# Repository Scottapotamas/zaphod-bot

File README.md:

# ZaphodBot Lightpainting Robot

ZaphodBot is a DIY, 'high-end' rotary delta robot designed primarily for high-fidelity light painting.

It's served as a personal project where the majority of mechanics, electronics, firmware and higher level software has been designed from scratch (because why not).

I've detailed the design motivation and build in a more [longform post here](https://electricui.com/blog/delta-bot).

## Mechanics

CAD files for the robot are in Solidworks 2015 format, and can be found in `/mechanical/design/`.

The power supply and main electronics stacks live inside the hexagonal structure which forms the base, with servos mounted on top, connected directly to the arms.

To manufacture parts, see `/mechanical/design/manf_outputs/`  for drawings, STEP/DXF files. SLA 3D printing was used for joints, and CNC machining for the aluminium parts and carbon plates. 

All fasteners are standard metric hex bolts, with the exception of some bottom mounting holes which are 1/4in and 3/8in threaded holes to suit typical camera tripods.

## Electronics

The PCB was designed using KiCAD 5, located in `electronics/zaphod-controller`. Gerber outputs are available with BoM, but minor design revisions are needed to improve wire-loom layout and debug/expansion connector positions. 

It's based on a STM32F4 processor, provides regulated 3/5/12V from the 75V system supply, and manages the servos, internal IO and external IO.

- Power input (75V from Teknic IPC) through 2-pin MOLEX SABRE connector.
- Clearpath servo motors connect with 8-pin MOLEX MicroFit for signalling, and 4-pin MicroFit for 75V supply.
- Internal IO NanoFit connectors provide PWM fan support, UART, I2C, 2x ADC/DAC, and PWM. These can also be used as generic IO. See  `/electronics/zaphod-controller/Outputs/zaphod-controller-sch.pdf` for pinouts.
- Internal IO 2.54mm header strip provides switchable+fused 3.3V and USART, intended for wireless comms backpack in the future (likely ESP32 flavoured).
- The 9-pin LEMO connector used for external expansion provides galvanically isolated USB and 4 isolated IO lines (2 inputs, 2 outputs). Pinout in `/docs/connectors_pinouts.md`.
- The 7-pin LEMO connector supports a 4th Clearpath SD series servo, intended for use with rotating or linear stages. Pinout in `/docs/connectors_pinouts.md.`

## Firmware

Microcontroller firmware (STM32) is in `/firmware`, is written in C, and can be built with a fairly standard `arm-gcc-eabi-none` toolchain.

I've used (and included config for) CLion as my main IDE, which is CMake based, though building with SW4/Eclipse shouldn't be too hard either.

Flashing the microcontroller is pretty standard as well, a 10-pin ARM CORTEX SWD socket is on the PCB, which connects to a STLink, Blackmagic Probe, or JLink programmer (used all three at various stages of this project).

# User Interface

The user interface is built with [Electric UI](https://electricui.com/install), and can be built and run by invoking `arc start` from `/interface`. 

It facilitates control and monitoring of the hardware, along with toolpath generation, optimisation and visualisation pipelines.

## Toolpath Generation

Toolpaths for lightpainting are created by exporting spline data from [Blender using a Python script](https://github.com/Mike-Dax/total-perspective-vortex/blob/main/blender/addons/total_perspective_vortex/tpv.py), and loading the output with the "Blender" tab in the UI.

The frontend UI is responsible for parsing the Blender scene and performing a series of move planning and TSP optimisation steps to reduce render times.

https://user-images.githubusercontent.com/460325/182141536-1118c95f-b80b-4199-9833-aa961b41ea9a.mp4

> This screencap shows a Blender animation being loaded: the 'fast' plan completes within a second, then the multi-threaded TSP solver iterates on each frame to refine the path taken to render the particles.

# Accessories

## Light Painting

The light-painting 'brush' uses acrylic 1mm core fibre, connected to a 3x3W RGB LED.

The fibre is mounted to the effector with a turned acetal stalk (not documented), or with one of the SLA printed mounts found in `/mechanical/fibre-couplers/`.

The driver PCB is in `/electronics/rgb-led-board/` along with manufacturing files and a simple Arduino test program. This board connects to `zaphod-controller` via the 8-pin NanoFit connector, which provides PWM+IO and power.

## External E-STOP + IO Breakout Box

The 9-pin LEMO connector is used with a 2m cable, connecting to the breakout box via matching 9-pin LEMO. A [Novelkeys Big Switch](https://novelkeys.xyz/products/the-big-switch-series) is used as an E-STOP, with the keyswitch light indicating motor state.

A 2.5mm stereo socket mounted in the box provides support for camera shutter release cable, in this case for a Canon N3 connector.

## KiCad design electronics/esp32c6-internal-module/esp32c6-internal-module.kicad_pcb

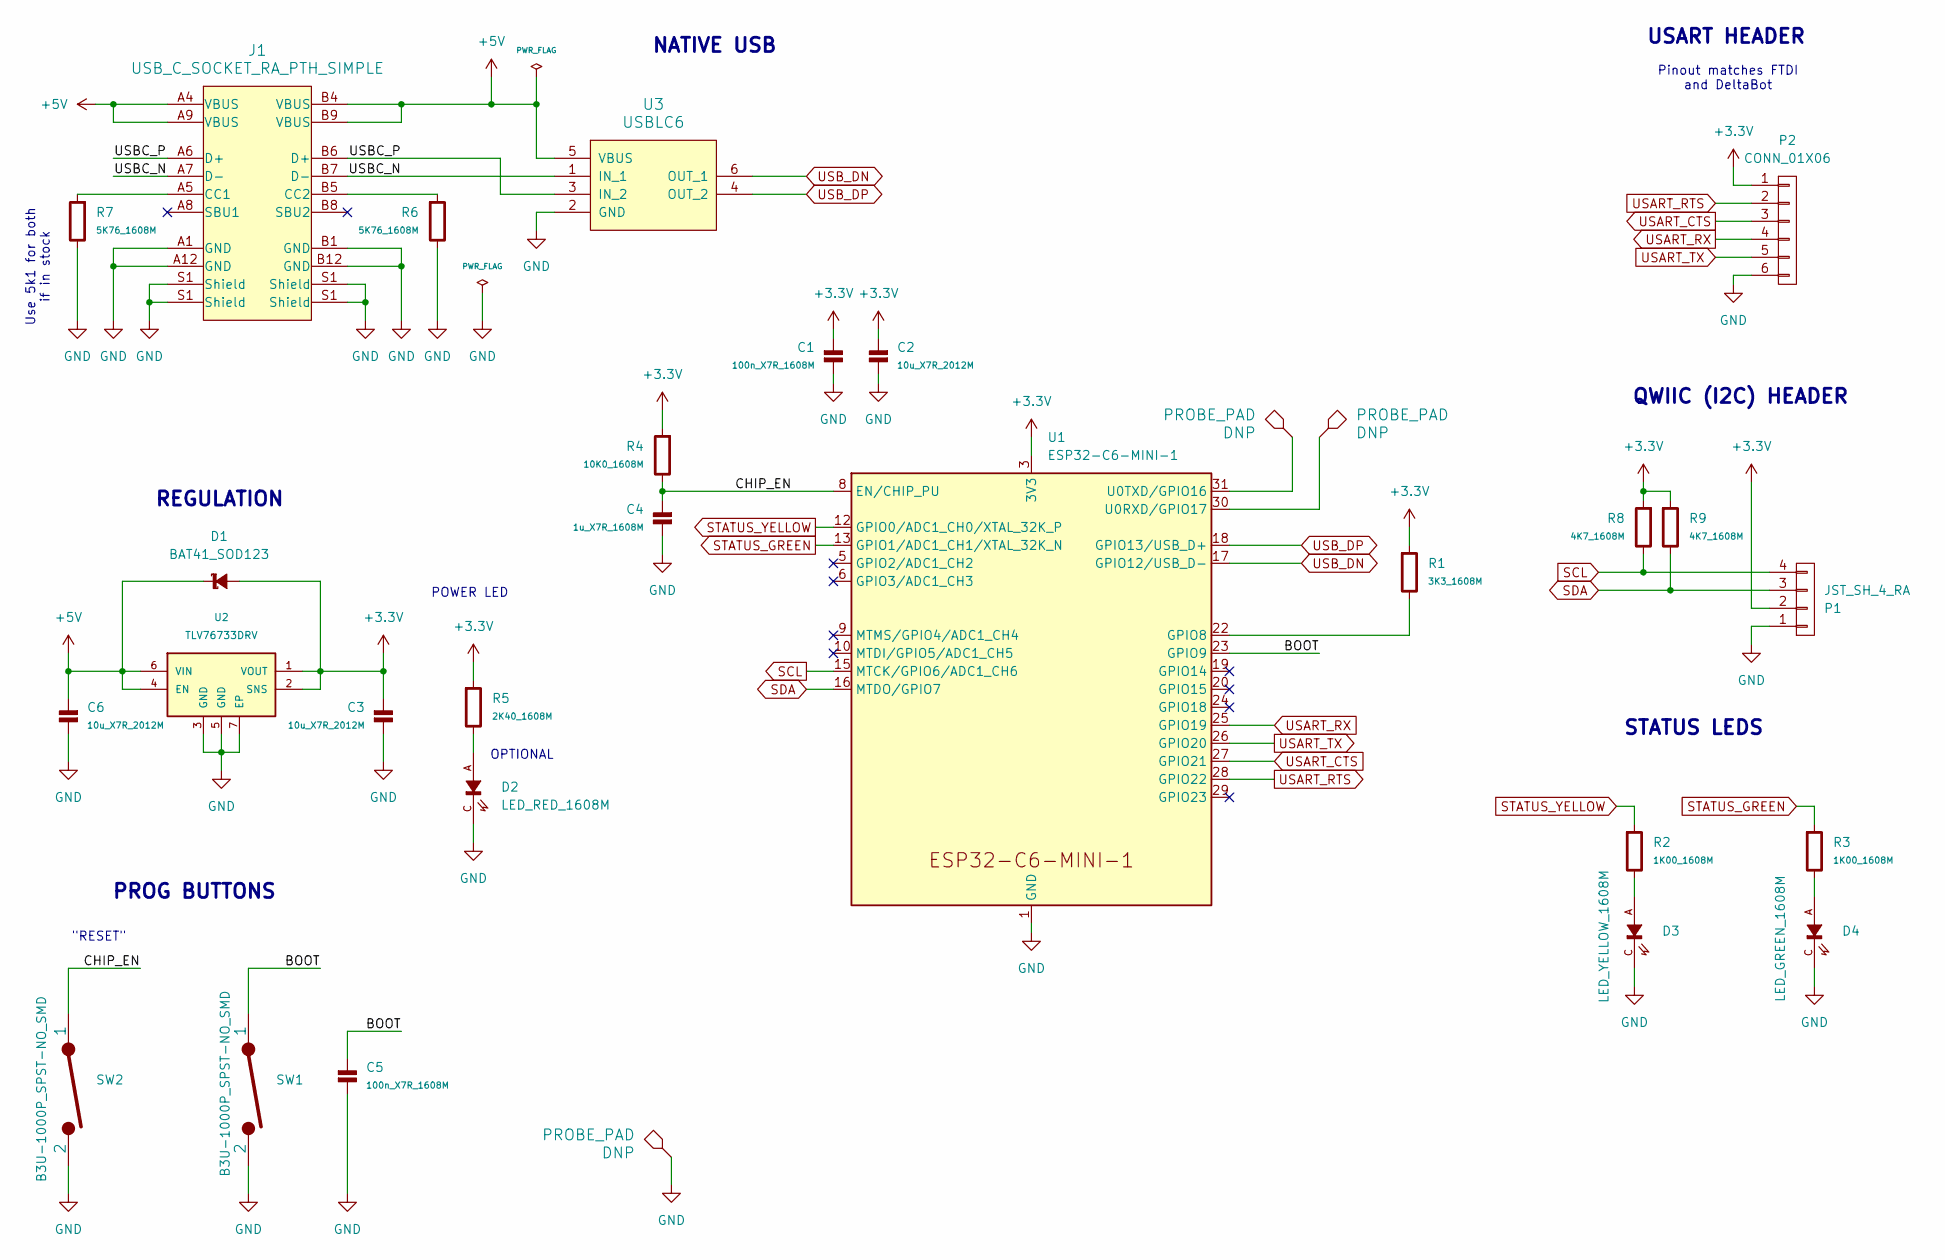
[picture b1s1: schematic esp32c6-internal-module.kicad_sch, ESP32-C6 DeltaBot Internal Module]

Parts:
C1, C5: 100n_X7R_1608M; CAPC1608X90N
C2, C3, C6: 10u_X7R_2012M; CAPC2012X110N
C4: 1u_X7R_1608M; CAPC1608X90N
D1: BAT41_SOD123; SOD3715X145L
D2: LED_RED_1608M; LEDC1608X80L40N
D3: LED_YELLOW_1608M; LEDC1608X80L40N
D4: LED_GREEN_1608M; LEDC1608X80L40N
J1: USB_C_SOCKET_RA_PTH_SIMPLE; USB_C_PTH_GCT_USB4085
P1: JST_SH_4_RA; SM04B-SRSS-TB
P2: CONN_01X06; 61300611121
R1: 3K3_1608M; RESC1608X50N
R2, R3: 1K00_1608M; RESC1608X50N
R4: 10K0_1608M; RESC1608X50N
R5: 2K40_1608M; RESC1608X50N
R6, R7: 5K76_1608M; RESC1608X50N
R8, R9: 4K7_1608M; RESC1608X50N
SW1, SW2: B3U-1000P_SPST-NO_SMD; B3U-1000P
TEST1, TEST2, TEST3: PROBE_PAD; TP100
U1: ESP32-C6-MINI-1
U2: TLV76733DRV; SON65P200X200X80-9T160X100N
U3: USBLC6; SOT95P280X145-6L50N

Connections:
+3.3V: C1.1, C2.1, C3.1, D1.A, P1.2, P2.1, R1.1, R4.1, R5.1, R8.1, R9.1, U1.3 (3V3), U2.1 (VOUT), U2.2 (SNS)
+5V: C6.1, D1.C, J1.A4 (VBUS), J1.A9 (VBUS), J1.B4 (VBUS), J1.B9 (VBUS), U2.4 (EN), U2.6 (VIN), U3.5 (VBUS)
/BOOT: C5.1, SW1.1, U1.23 (GPIO9)
/CHIP_EN: C4.1, R4.2, SW2.1, U1.8 (EN/CHIP_PU)
/USBC_N: J1.A7 (D-), J1.B7 (D-), U3.1 (IN_1)
/USBC_P: J1.A6 (D+), J1.B6 (D+), U3.3 (IN_2)
GND: C1.2, C2.2, C3.2, C4.2, C5.2, C6.2, D2.C, D3.C, D4.C, J1.A1 (GND), J1.A12 (GND), J1.B1 (GND), J1.B12 (GND), J1.S1 (Shield), P1.1, P2.6, R6.2, R7.2, SW1.2, SW2.2, TEST3.1 (PAD), U1.1 (GND), U1.2 (GND), U1.11 (GND), U1.14 (GND), U1.36 (GND), U1.37 (GND), U1.38 (GND), U1.39 (GND), U1.40 (GND), U1.41 (GND), U1.42 (GND), U1.43 (GND), U1.44 (GND), U1.45 (GND), U1.46 (GND), U1.47 (GND), U1.48 (GND), U1.49 (GND), U1.50 (GND), U1.51 (GND), U1.52 (GND), U1.53 (GND), U2.3 (GND), U2.5 (GND), U2.7 (EP), U3.2 (GND)
unnamed: D3.A, R2.2
unnamed: D4.A, R3.2
unnamed: D2.A, R5.2
unnamed: J1.A5 (CC1), R7.1
unnamed: J1.B5 (CC2), R6.1
unnamed: TEST1.1 (PAD), U1.31 (U0TXD/GPIO16)
unnamed: TEST2.1 (PAD), U1.30 (U0RXD/GPIO17)
unnamed: R1.2, U1.22 (GPIO8)
SCL: P1.4, R8.2, U1.15 (MTCK/GPIO6/ADC1_CH6)
SDA: P1.3, R9.2, U1.16 (MTDO/GPIO7)
STATUS_GREEN: R3.1, U1.13 (GPIO1/ADC1_CH1/XTAL_32K_N)
STATUS_YELLOW: R2.1, U1.12 (GPIO0/ADC1_CH0/XTAL_32K_P)
USART_CTS: P2.3, U1.27 (GPIO21)
USART_RTS: P2.2, U1.28 (GPIO22)
USART_RX: P2.4, U1.25 (GPIO19)
USART_TX: P2.5, U1.26 (GPIO20)
USB_DN: U1.17 (GPIO12/USB_D-), U3.6 (OUT_1)
USB_DP: U1.18 (GPIO13/USB_D+), U3.4 (OUT_2)

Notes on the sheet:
NATIVE USB
PROG BUTTONS
Pinout matches FTDI and DeltaBot
"RESET"
QWIIC (I2C) HEADER
OPTIONAL
REGULATION
USART HEADER
Use 5k1 for both if in stock
POWER LED
STATUS LEDS

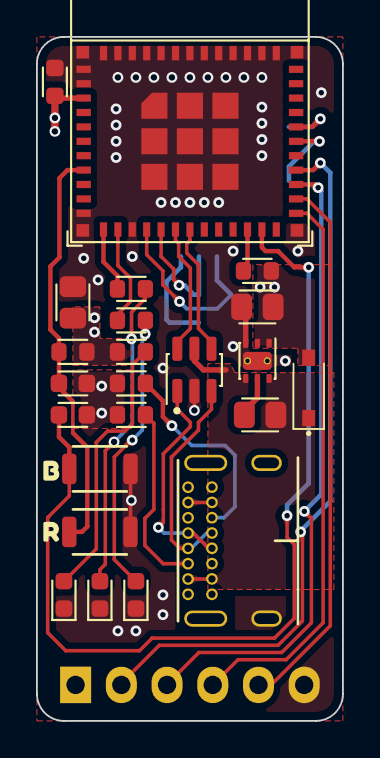
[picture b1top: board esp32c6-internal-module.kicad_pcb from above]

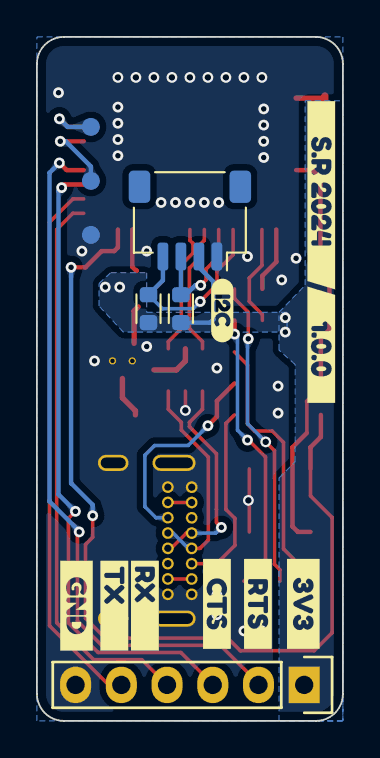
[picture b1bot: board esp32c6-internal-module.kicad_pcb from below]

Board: 2 copper layers, 17.0 x 38.0 mm, 41 parts (16 on the bottom side), 25 nets.

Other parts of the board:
kibuzzard-667148AD: G***; kibuzzard-667148AD
kibuzzard-667148E1: G***; kibuzzard-667148E1
kibuzzard-6671475C: G***; kibuzzard-6671475C
kibuzzard-6671480C: G***; kibuzzard-6671480C
kibuzzard-6671482E: G***; kibuzzard-6671482E
kibuzzard-66714795: G***; kibuzzard-66714795
kibuzzard-66714802: G***; kibuzzard-66714802
kibuzzard-66714835: G***; kibuzzard-66714835
kibuzzard-66714898: G***; kibuzzard-66714898
kibuzzard-66714909: G***; kibuzzard-66714909
kibuzzard-66714928: G***; kibuzzard-66714928

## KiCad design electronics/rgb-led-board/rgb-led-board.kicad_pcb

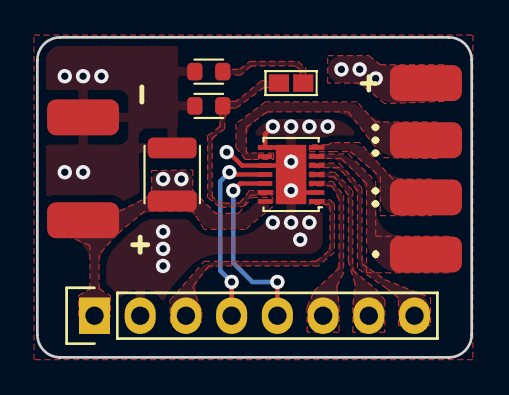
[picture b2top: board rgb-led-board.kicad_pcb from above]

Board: 2 copper layers, 24.1 x 17.8 mm, 12 parts (0 on the bottom side), 13 nets.

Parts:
C1: 22u_X7R_3225M; CAPC3225X170N
P1, P2, P4, P5, P6, P7: PAD_SOLDER_2mm
P3: CONN_01X08; 61300811121
R1, R2: 12K7_1608M; RESC1608X50N
SL1: SOLDER-LINK-2; SJ1608-2N
U1: AL1793AFE-13; QFN14P50_400X300X65L40X25N

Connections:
+POWER: C1.1, P1.1, P3.1, P4.1, U1.14
/ENABLE: P3.3, U1.1
/LED_1: P5.1, U1.6
/LED_2: P6.1, U1.7
/LED_3: P7.1, U1.9
/POWER_GOOD: P3.4, U1.11
/PWM1: P3.8, U1.5
/PWM2: P3.7, U1.4
/PWM3: P3.6, U1.3
/~FAULT: P3.5, U1.12
GND: C1.2, P2.1, P3.2, R1.2, R2.2, U1.2, U1.8, U1.10, U1.15
unnamed: R1.1, SL1.1
unnamed: R2.1, SL1.2, U1.13

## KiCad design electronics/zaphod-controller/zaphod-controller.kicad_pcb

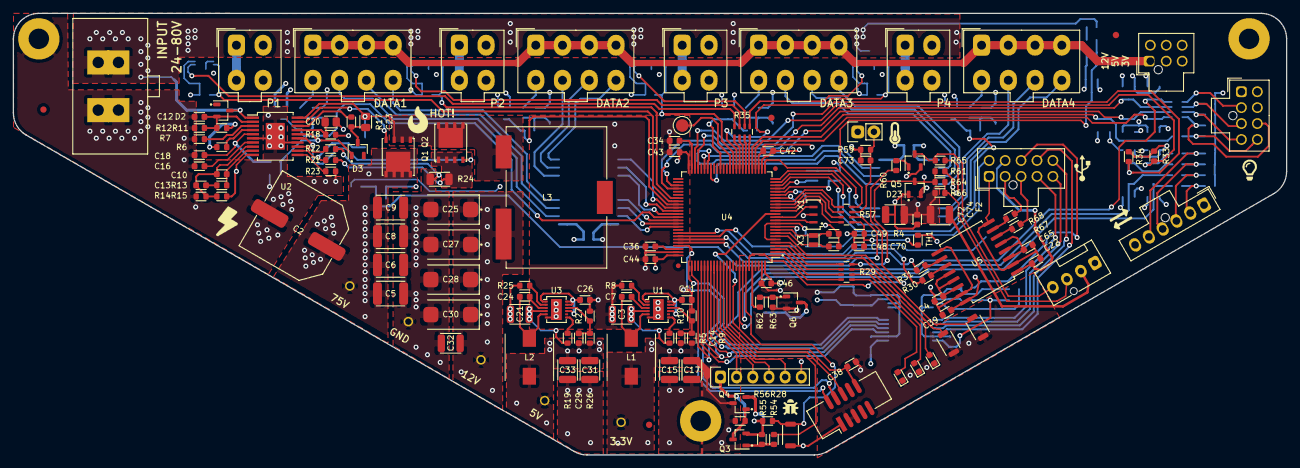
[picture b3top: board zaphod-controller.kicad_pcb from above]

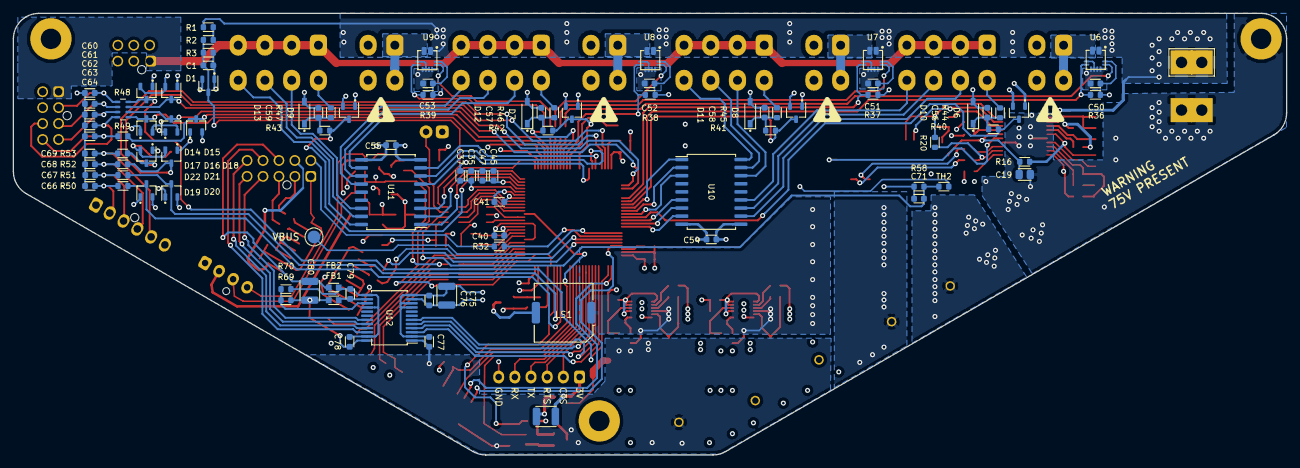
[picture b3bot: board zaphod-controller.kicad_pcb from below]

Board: 4 copper layers, 199.9 x 69.3 mm, 251 parts (97 on the bottom side), 182 nets.

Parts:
C1, C4, C7, C16, C22, C24, C37, C38, C39, C40, C41, C42, C43, C44, C46, C47, C50, C51, C52, C53, C54, C55, C65, C70, C71, C73, C74, C76, C77, C78, C79: 100n_X7R_1608M; CAPC1608X90N
C2: 47u_ELEC_100V_1350X1350M; CAPAE1350X1350D1490DD450L470N
C3, C21, C75, C80: 10u_X7R_3225M; CAPC3225X170N
C5, C6, C8, C9: 2u2_X7R_4532M; CAPC4532X180N
C10: 15p_X7R_1608M; CAPC1608X90N
C11, C12, C26, C34, C35, C36, C45: 1u_X7R_1608M; CAPC1608X90N
C13: 1n5_X7R_1608M; CAPC1608X90N
C14, C29, C48, C49: 22p_X7R_1608M; CAPC1608X90N
C15, C17, C31, C32, C33, C72: 22u_X7R_3225M; CAPC3225X170N
C18: 330p_X7R_1608M; CAPC1608X90N
C19, C20, C23: 1u_X7R_2012M; CAPC2012X110N
C25, C27, C28, C30: 47u_TANT_7343M; CAPPM7343X310N
C56, C57, C58, C59: 10n_X7R_1608M; CAPC1608X90N
C60, C61, C62, C63, C64, C66, C67, C68, C69: 1n_X7R_1608M; CAPC1608X90N
D1, D6, D7, D8, D9, D14, D15, D16, D17, D18, D19, D20, D21, D22, D23: BAV99; SOT95P240X110-3L16N
D2, D3: 200V_350mW_SOT23; SOT95P240X110-3L16N
D4: LED_YELLOW_1608M; LEDC1608X80L40N
D5: LED_GREEN_1608M; LEDC1608X80L40N
D10, D11, D12, D13: 3V3; SOD3715X145N
D24: LED_RED_1608M; LEDC1608X80L40N
F1, F2: 0.5A_1210L_PTC; FUSC3225X85L50N
FB1, FB2: 1K_1608M; INDC1608X95N
FID1, FID2, FID3, FID4: FIDUCIAL; FID100X200
L1, L2: 22u_MCSDRH73B; INDM7373X355L170X207N
L3: 10u2_PA2050; PULSE_PA2050
LOGO1: LOGO; PANIC_LOGO890X810
LOGO2: LOGO; BUG_LOGO250X250
LOGO3: LOGO; BULB_LOGO230X330
LOGO4: LOGO; THERMO_LOGO_170X350
LOGO5: LOGO; USB_LOGO410X250
LOGO6, LOGO7, LOGO8, LOGO9: LOGO; WARN_TRIANGLE_LOGO440X400
LOGO10: LOGO; WARN_TRIANGLE_LOGO440X400_MASK
LOGO11: LOGO; FIRE_LOGO_320X420
LOGO12: LOGO; BOLT_LOGO_310X490
LOGO13: LOGO; DUPLEX_LOGO330X260
LS1: PKMCS0909E4000-R1; MURATA_PKMCS0909E4000
MNT1, MNT2, MNT3: MNT_M3_PLATED; MTGP650H330
P1: MOLEX_43160-0102; Molex_Sabre_43160-0102_VERT
P2, P3, P4, P5: MOLEX_MINIFIT_JR_2x2_WAY; Molex_Mini-Fit_Jr_5566-04A_2x02_P4.20mm_Vertical
P11, P12, P13, P14: MOLEX_MINIFIT_JR_2x4_WAY; Molex_Mini-Fit_Jr_5566-08A_2x04_P4.20mm_Vertical
P15: MOLEX_NANOFIT_2x4_WAY; Molex_Nano-Fit_105310-xx08_2x04_VERT
P16: MOLEX_NANOFIT_1x6_WAY; Molex_Nano-Fit_105309-xx06_1x06_VERT
P17: MOLEX_NANOFIT_2x3_WAY; Molex_Nano-Fit_105310-xx06_2x03_VERT
P18: CONN_01X02; 61300211121
P19: MOLEX_KK2.54_1x4_WAY_FAN; MOLEX_47053-1000
P20: CONN_01X06; 61300611121
P21: MOLEX_NANOFIT_2x5_WAY; Molex_Nano-Fit_105310-xx10_2x05_VERT
Q1, Q2: Si7852DP; SON127P490X575X90-9T313X381N
Q3, Q6: 2N7002P; SOT95P240X110-3L16N
Q4: NTR1P02T1G; SOT95P240X110-3L16N
Q5: BC847B; SOT95P240X110-3L16N
R1, R2: 130K_1608M; RESC1608X50N
R3, R23, R36, R37, R38, R39, R55, R56, R61, R63, R70: 10K0_1608M; RESC1608X50N
R4, R58, R59: 2K40_1608M; RESC1608X50N
R5, R8, R9, R19, R25, R28: 100K_1608M; RESC1608X50N
R6: 1M_1608M; RESC1608X50N
R7, R27: 12K7_1608M; RESC1608X50N
R10, R44, R45, R46, R47: 22K_1608M; RESC1608X50N
R11: 102K_1608M; RESC1608X50N
R12: 9K53_1608M; RESC1608X50N
R13: 39K_1608M; RESC1608X50N
R14: 1K2_1608M; RESC1608X50N
R15: 10K7_1608M; RESC1608X50N
R16: 750K_1608M; RESC1608X50N
R17: 2R2_1608M; RESC1608X50N
R18: 1R0_1608M; RESC1608X50N
R20, R21, R22: 0R_1608M; RESC1608X50N
R24: R01_3216M; RESC3216X140N
R26: 91K_1608M; RESC1608X50N
R29, R35, R57: 1K_QUAD_ARRAY_1608M; R_Array_Concave_4x1608M
R30, R31, R67, R68: 22R_1608M; RESC1608X50N
R32, R40, R41, R42, R43, R50, R51: 100R_1608M; RESC1608X50N
R33, R34, R65, R66: 4K7_1608M; RESC1608X50N
R48: 47R_QUAD_ARRAY_1608M; R_Array_Concave_4x1608M
R49, R52, R53, R54, R62: 10R_1608M; RESC1608X50N
R60: 1K00_1608M; RESC1608X50N
R64: 33K2_1608M; RESC1608X50N
R69: 16K9_1608M; RESC1608X50N
SW1, SW2, SW3: B3U-1000P_SPST-NO_SMD; B3U-1000P
TEST1: CLIP_HOOK_BROWN; KEYSTONE_5115
TEST2: CLIP_HOOK_YELLOW; KEYSTONE_5004
TEST3: CLIP_HOOK_RED; KEYSTONE_5000
TEST4: CLIP_HOOK_ORANGE; KEYSTONE_5003
TEST5: CLIP_HOOK_BLACK; KEYSTONE_5001
TEST6, TEST8: PROBE_PAD; TP200
TH1, TH2: NTC_10K_1608M; RESC1608X50N
U1, U3: ISL85410FRZ; QFN50P400X300X100-13T170X330N
U2: LM5116; SOP21P65_720X780X200L75X30N
U4: STM32F429VET6; QFP50P1600X1600X160-100L25N
U5: ADUM3160; SOIC127P1032X265-16L87N
U6, U7, U8, U9: ACS711KEXLT_15AB; ACS-EX-12
U10, U11: ULN2003A; SOIC127P1030X265-18L87N
U12: ADUM5412; SOP65P780X200-24L40N
X1: CSTCE8M00G55Z; OSCSC-CSCTE-CERALOCK
X2: SWD_SMT_SOCKET; CNCTECH_3220-10-0300-00
X3: ABS06-107-32.768KHZ; XTALDFN200X120X60-2N

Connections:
+3.3V: C14.1, C15.1, C17.1, C35.1, C37.1, C39.2, C40.1, C41.1, C42.1, C43.1, C44.1, C45.1, C46.1, C47.1, C50.2, C51.2, C52.2, C53.2, C77.2, D1.2, D6.2, D7.2, D8.2, D9.2, D14.2, D15.2, D16.2, D17.2, D18.2, D19.2, D20.2, D21.2, D22.2, D23.2, L1.1, P15.6, P16.1, P17.3, P18.1, Q4.3, R9.1, R33.2, R34.1, R36.2, R37.2, R38.2, R39.2, R56.1, SW1.2, TEST4.1, TH1.1, TH2.1, U4.6, U4.11, U4.19, U4.21, U4.22, U4.28, U4.50, U4.75, U4.100, U5.16, U6.12, U7.12, U8.12, U9.12, U12.1, X2.1
+5V: C29.1, C31.1, C33.1, C75.2, C76.2, L2.1, P17.2, R26.1, R65.2, TEST3.1, U12.11
+12V: C3.2, C21.2, C25.1, C27.1, C28.1, C30.1, C32.1, C54.2, C55.2, C72.2, C74.2, F2.2, L3.2, LS1.1, P11.1, P11.2, P11.3, P11.4, P12.1, P12.2, P12.3, P12.4, P13.1, P13.2, P13.3, P13.4, P14.1, P14.2, P14.3, P14.4, P15.1, P17.1, R5.2, R15.1, R18.1, R19.2, R66.2, TEST2.1, U1.4, U2.10, U3.4, U10.10, U11.10
+POWER: C2.1, C5.1, C6.1, C8.1, C9.1, D2.3, P1.1, Q1.3, R1.2, R6.2, R11.1, TEST1.1, U2.1, U6.1, U7.1, U8.1, U9.1
/Expansion I/O/ISO_IN_0: P21.5, U12.20
/Expansion I/O/ISO_IN_1: P21.4, U12.19
/Expansion I/O/ISO_IO_GND: C80.1, FB2.1, P21.8
/Expansion I/O/ISO_OUT_0: P21.9, U12.22
/Expansion I/O/ISO_OUT_1: P21.10, U12.21
/Output Circuits and Connectors/M1_PWR: P2.1, P2.3, U6.4
/Output Circuits and Connectors/M2_PWR: P3.1, P3.3, U7.4
/Output Circuits and Connectors/M3_PWR: P4.1, P4.3, U8.4
/Output Circuits and Connectors/M4_PWR: P5.1, P5.3, U9.4
AUX_ANALOG_0: D17.3, R48.5, U4.29
AUX_ANALOG_1: D18.3, R49.2, U4.30
AUX_PWM_0: D14.3, R48.8, U4.77
AUX_PWM_1: D15.3, R48.7, U4.53
AUX_PWM_2: D16.3, R48.6, U4.54
BOOT0: R28.1, SW1.1, U4.94
BOOT1: TEST8.1, U4.37
BUTTON_0: SW2.2, U4.7
BUTTON_1: SW3.2, U4.5
BUZZER_PWM: R62.2, U4.96
EXT_INPUT_0: U4.83, U12.5
EXT_INPUT_1: U4.81, U12.6
EXT_OUTPUT_0: U4.80, U12.3
EXT_OUTPUT_1: U4.82, U12.4
FAN_HALL: R29.1, U4.4
FAN_PWM: R60.2, U4.95
GND: C1.2, C2.2, C3.1, C4.1, C5.2, C6.2, C8.2, C9.2, C11.1, C12.1, C15.2, C16.2, C17.2, C18.2, C19.1, C20.1, C21.1, C25.2, C26.1, C27.2, C28.2, C30.2, C31.2, C32.2, C33.2, C34.2, C35.2, C36.2, C37.2, C38.2, C39.1, C40.2, C41.2, C42.2, C43.2, C44.2, C45.2, C46.2, C47.2, C48.2, C49.2, C50.1, C51.1, C52.1, C53.1, C54.1, C55.1, C56.1, C57.1, C58.1, C59.1, C60.2, C61.2, C62.2, C63.2, C64.2, C66.2, C67.2, C68.2, C69.2, C70.1, C71.1, C72.1, C73.1, C74.1, C75.1, C76.1, C77.1, D1.1, D4.C, D5.C, D6.1, D7.1, D8.1, D9.1, D10.A, D11.A, D12.A, D13.A, D14.1, D15.1, D16.1, D17.1, D18.1, D19.1, D20.1, D21.1, D22.1, D23.1, D24.C, MNT1.1, MNT2.1, MNT3.1, P1.2, P2.2, P2.4, P3.2, P3.4, P4.2, P4.4, P5.2, P5.4, P15.5, P16.6, P17.4, P17.5, P17.6, P19.1, P20.6, Q3.2, Q5.2, Q6.2, R3.1, R4.2, R7.1, R8.2, R10.2, R12.2, R14.2, R22.1, R23.1, R24.2, R25.2, R27.2, R28.2, R55.2, R58.2, R59.2, R61.2, R63.2, SW2.1, SW3.1, TEST5.1, U1.6, U1.EP, U2.6, U2.14, U2.EP, U3.6, U3.EP, U4.10, U4.20, U4.27, U4.74, U4.99, U5.9, U5.15, U6.5, U6.7, U6.8, U6.9, U6.10, U7.5, U7.7, U7.8, U7.9, U7.10, U8.5, U8.7, U8.8, U8.9, U8.10, U9.5, U9.7, U9.8, U9.9, U9.10, U10.9, U11.9, U12.2, U12.9, U12.10, U12.12, X1.2, X2.3, X2.5
I2C_SCK: D21.3, R34.2, R52.2, U4.47
I2C_SDA: D22.3, R33.1, R53.2, U4.48
ID_SPARE: P21.6, R32.2
ISOLATED_D+: P21.2, R68.1
ISOLATED_D-: P21.3, R67.1
ISOLATED_USB_GND: C22.1, C65.1, P21.1, U5.2, U5.8
ISOLATED_USB_VDD: C22.2, P21.7, U5.1
MOTOR_1_CURRENT: R35.5, U4.34
MOTOR_2_CURRENT: R35.6, U4.33
MOTOR_3_CURRENT: R35.7, U4.32
MOTOR_4_CURRENT: R35.8, U4.31
NRST: C38.1, U4.14, X2.10
unnamed: C1.1, D1.3, R2.1, R3.2, R57.4
unnamed: C4.2, U5.12, U5.13, U5.14
unnamed: C7.1, U1.3
unnamed: C7.2, L1.2, U1.5
unnamed: C10.1, R13.1, U2.9
unnamed: C10.2, C13.1, R14.1, R15.2, U2.8
unnamed: C11.2, U1.1, U1.9, U1.11, U1.12
unnamed: C12.2, D2.2, R11.2, R12.1, U2.2
unnamed: C13.2, R13.2
unnamed: C14.2, R9.2, R10.1, U1.10
unnamed: C16.1, U2.7
unnamed: C18.1, R16.2, U2.5
unnamed: C19.2, D3.1, R16.1, U2.16
unnamed: C20.2, R18.2, U2.17
unnamed: C23.1, L3.1, Q1.2, Q2.3, R20.1, U2.20
unnamed: C23.2, D3.3, R17.2
unnamed: C24.1, U3.3
unnamed: C24.2, L2.2, U3.5
unnamed: C26.2, U3.1, U3.9, U3.11, U3.12
unnamed: C29.2, R26.2, R27.1, U3.10
unnamed: C34.1, U4.49
unnamed: C36.1, U4.73
unnamed: C48.1, U4.8, X3.1
unnamed: C49.1, U4.9, X3.2
unnamed: C56.2, D10.C, R40.1, R44.2
unnamed: C57.2, D12.C, R42.1, R46.2
unnamed: C58.2, D11.C, R41.1, R45.2
unnamed: C59.2, D13.C, R43.1, R47.2
unnamed: C60.1, P15.2, R48.1
unnamed: C61.1, P15.3, R48.2
unnamed: C62.1, P15.4, R48.3
unnamed: C63.1, P15.7, R48.4
unnamed: C64.1, P15.8, R49.1
unnamed: C65.2, U5.3, U5.4, U5.5
unnamed: C66.1, P16.2, R50.1
unnamed: C67.1, P16.3, R51.1
unnamed: C68.1, P16.4, R52.1
unnamed: C69.1, P16.5, R53.1
unnamed: C70.2, R4.1, R57.1, TH1.2
unnamed: C71.2, R57.2, R58.1, TH2.2
unnamed: C73.2, P18.2, R57.3, R59.1
unnamed: C78.1, C79.1, FB2.2, R70.1, U12.13, U12.16, U12.23
unnamed: C78.2, C80.2, FB1.1, R69.1, U12.24
unnamed: C79.2, FB1.2, U12.14
unnamed: D4.A, R29.6
unnamed: D5.A, R29.5
unnamed: D23.3, R29.8, R61.1, R64.2
unnamed: D24.A, R29.7
unnamed: F1.1, P20.1
unnamed: F1.2, Q4.2
unnamed: F2.1, P19.2
unnamed: LS1.2, Q6.3
unnamed: P11.5, R44.1
unnamed: P11.6, U10.11
unnamed: P11.7, U10.12
unnamed: P11.8, U10.13
unnamed: P12.5, R45.1
unnamed: P12.6, U10.16
unnamed: P12.7, U10.17
unnamed: P12.8, U10.18
unnamed: P13.5, R46.1
unnamed: P13.6, U11.11
unnamed: P13.7, U11.12
unnamed: P13.8, U11.13
unnamed: P14.5, R47.1
unnamed: P14.6, U11.16
unnamed: P14.7, U11.17
unnamed: P14.8, U11.18
unnamed: P19.3, R64.1, R66.1
unnamed: P19.4, Q5.3, R65.1
unnamed: Q1.1, U2.19
unnamed: Q2.1, U2.15
unnamed: Q2.2, R21.1, R24.1
unnamed: Q3.1, R54.1, R55.1
unnamed: Q3.3, Q4.1, R56.2
unnamed: Q5.1, R60.1
unnamed: Q6.1, R62.1, R63.1
unnamed: R1.1, R2.2
unnamed: R5.1, U1.7
unnamed: R6.1, U2.4
unnamed: R7.2, U2.3
unnamed: R8.1, U1.2
unnamed: R17.1, U2.18
unnamed: R19.1, U3.7
unnamed: R20.2, R21.2, U2.12
unnamed: R22.2, U2.13
unnamed: R23.2, U2.11
unnamed: R25.1, U3.2
unnamed: R30.1, U5.11
unnamed: R31.1, U5.10
unnamed: R35.1, U9.11
unnamed: R35.2, U8.11
unnamed: R35.3, U7.11
unnamed: R35.4, U6.11
unnamed: R67.2, U5.6
unnamed: R68.2, U5.7
unnamed: R69.2, R70.2, U12.15
unnamed: U4.12, X1.1
unnamed: U4.13, X1.3
SERVO1_A: U4.65, U10.7
SERVO1_B: U4.66, U10.8
SERVO1_EN: U4.64, U10.6
SERVO1_HLFB: D6.3, R40.2, U4.63
SERVO2_A: U4.61, U10.2
SERVO2_B: U4.62, U10.3
SERVO2_EN: U4.60, U10.1
SERVO2_HLFB: D8.3, R41.2, U4.59
SERVO3_A: U4.44, U11.7
SERVO3_B: U4.45, U11.8
SERVO3_EN: U4.43, U11.6
SERVO3_HLFB: D7.3, R42.2, U4.40
SERVO4_A: U4.25, U11.2
SERVO4_B: U4.26, U11.3
SERVO4_EN: U4.24, U11.1
SERVO4_HLFB: D9.3, R43.2, U4.23
STATUS_0: R29.2, U4.3
STATUS_1: R29.3, U4.2
STATUS_2: R29.4, U4.1
SWCLK: U4.76, X2.4
SWDIO: U4.72, X2.2
SWO: U4.89, X2.6
TEMP_EXT_0: R57.7, U4.16
TEMP_EXT_1: R57.6, U4.17
TEMP_PCB: R57.8, U4.15
USART_1_RX: D20.3, R51.2, U4.93
USART_1_TX: D19.3, R50.2, U4.92
USART_2_CTS: P20.2, U4.84
USART_2_PWR_EN: R54.2, U4.88
USART_2_RTS: P20.3, U4.85
USART_2_RX: P20.5, U4.87
USART_2_TX: P20.4, U4.86
USB_D+: R31.2, U4.71
USB_D-: R30.2, U4.70
USB_OTG_ID: R32.1, U4.69
USB_VBUS: TEST6.1, U4.68
VOLTAGE_INPUT: R57.5, U4.18
~MOTOR_1_OC: R36.1, U4.58, U6.6
~MOTOR_2_OC: R37.1, U4.57, U7.6
~MOTOR_3_OC: R38.1, U4.36, U8.6
~MOTOR_4_OC: R39.1, U4.35, U9.6

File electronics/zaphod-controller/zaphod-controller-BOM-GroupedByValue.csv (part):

Ref,Qty,Value,Description,Manf,Manf#,Installed,Footprint
"C1, C4, C7, C16, C22, C24, C37, C38, C39, C40, C41, C42, C43, C44, C46, C47, C50, C51, C52, C53, C54, C55, C65, C70, C71, C73, C74, C76, C77, C78, C79",31,100n_X7R_1608M,"CAP, MLCC, X7R, 100NF, 50V, 0603",KEMET,C0603C104K5RACAUTO, ,CAPC1608X90N
C10,1,15p_X7R_1608M,"CAP, MLCC, C0G/NP0, 15PF, 50V, 5%, 0603, 1608M",TDK,C1608C0G1H150J080AA, ,CAPC1608X90N
"C11, C12, C26, C34, C35, C36, C45",7,1u_X7R_1608M,"CAP, MLCC, X7R, 1UF, 50V, 0603",muRata,GRM188R61H105KAALD,b,CAPC1608X90N
C13,1,1n5_X7R_1608M,"CAP, MLCC, X7R, 1500PF, 50V, 10%, 0603, 1608M",muRata,GRM188R71H152KA01D, ,CAPC1608X90N
"C14, C29, C48, C49",4,22p_X7R_1608M,"CAP, MLCC, X7R, 22PF, 50V, 0603",MULTICOMP,MC0603N220K500CT, ,CAPC1608X90N
"C15, C17, C31, C32, C33, C72",6,22u_X7R_3225M,"CAP, MLCC, X7R, 22UF, 25V, 10%, 1210, 3225M",muRata,C1210C226K3RACTU,b,CAPC3225X170N
C18,1,330p_X7R_1608M,"CAP, MLCC, X7R, 330PF, 50V, 0603, 1608M",AVX,06035A331JAT2A, ,CAPC1608X90N
"C19, C20, C23",3,1u_X7R_2012M,"CAP, MLCC, X7R, 1UF, 16V, 0805, 2012M",muRata,GRM21BR71C105KA01L, ,CAPC2012X110N
C2,1,47u_ELEC_100V_1350X1350M,"CAP, ALU ELEC, 47UF, 100V, 320mOhm, AEC-Q200, 5000 hour, SMD",PANASONIC,EEV-FK2A470Q,b,CAPAE1350X1350D1490DD450L470N
"C25, C27, C28, C30",4,47u_TANT_7343M,"CAP, TANT, 47UF, 16V, 7343-31",KEMET,T520D476M016ATE035,b,CAPPM7343X310N
"C3, C21, C75, C80",4,10u_X7R_3225M,"CAP, MLCC, X7R, 10UF, 25V, 1210 3225M",WURTH ELEKTRONIK,885012209028, ,CAPC3225X170N
"C5, C6, C8, C9",4,2u2_X7R_4532M,"CAP, MLCC, X7R, 2.2UF, 100V, 1812, 4532M",TDK,C4532X7R2A225M230KA,b,CAPC4532X180N
"C56, C57, C58, C59",4,10n_X7R_1608M,"CAP, MLCC, X7R, 10NF, 25V, 0603",AVX,06033C103KAT2A, ,CAPC1608X90N
"C60, C61, C62, C63, C64, C66, C67, C68, C69",9,1n_X7R_1608M,"CAP, MLCC, X7R, 1NF, 100V, 0603",AVX,06031C102KAT2A, ,CAPC1608X90N
"D1, D6, D7, D8, D9, D14, D15, D16, D17, D18, D19, D20, D21, D22, D23",15,BAV99,"DIODE DUAL, 100V, 215mA, 4ns, SOT23",NXP,BAV99,b,SOT95P240X110-3L16N
"D10, D11, D12, D13",4,3V3,"DIODE, Zener 3V3, 500mW, SOD123",VISAY SEMICONDUCTOR,MMSZ5226, ,SOD3715X145N
"D2, D3",2,200V_350mW_SOT23,"CMPD2003C DIODE DUAL, Common Cathode, 200V, 200mA, 4A peak, 350mW, SOT23-3",Central Semiconductor,CMPD2003C-TR,b,SOT95P240X110-3L16N
D24,1,LED_RED_1608M,"DIALIGHT ChipLED Red, 0603, 1608M",DIALIGHT,5988010107F, ,LEDC1608X80L40N
D4,1,LED_YELLOW_1608M,"DIALIGHT ChipLED Yellow, 0603, 1608M",DIALIGHT,5988040107F, ,LEDC1608X80L40N
D5,1,LED_GREEN_1608M,"DIALIGHT ChipLED Green, 0603, 1608M",DIALIGHT,5988070107F, ,LEDC1608X80L40N
"F1, F2",2,0.5A_1210L_PTC,"FUSE, RESETTABLE, PTC, 13.2VDC, 500mA, SMD, 1210L050",LittelFuse, 1210L050YR,b,FUSC3225X85L50N
"FB1, FB2",2,1K_1608M,"FERRITE BEAD, 1Kohm @ 100MHz, 0.6Ohm, 100mA, 0603, 1608M",muRata,BLM18TG102TN1D,b,INDC1608X95N
"L1, L2",2,22u_MCSDRH73B,"INDUCTOR, 22UH, 1.83A, Shielded, 0.13ohm",MULTICOMP,MCSDRH73B-220MHF, ,INDM7373X355L170X207N
L3,1,10u2_PA2050,"INDUCTOR, 10.2UH, 12.5A, 10%, 0.0058ohm",PULSE ELECTRONICS,PA2050.103NL,b,PULSE_PA2050
LS1,1,PKMCS0909E4000-R1,"Murata Buzzer, passive, piezo transducer, 12V, 9x9x1.9mm, SMD, top firing",muRata,PKMCS0909E4000-R1,b,MURATA_PKMCS0909E4000
P1,1,MOLEX_43160-0102,"AS7.5mm pitch, Vertical, PTH, 2 contacts",MOLEX,043160-0102,b,Molex_Sabre_43160-0102_VERT
"P11, P12, P13, P14",4,MOLEX_MINIFIT_JR_2x4_WAY,"CONNECTOR, SOCKET, 8POS, 2ROW, MINI-FIT JR, 5566 series, 4.2MM pitch, PTH",MOLEX,172447-0208,b,Molex_Mini-Fit_Jr_5566-08A_2x04_P4.20mm_Vertical
P15,1,MOLEX_NANOFIT_2x4_WAY,"CONNECTOR, SOCKET, 8POS, 2ROW, Nano-fit, 105310 series, 2.5MM pitch, PTH",MOLEX,105310-1108,b,Molex_Nano-Fit_105310-xx08_2x04_VERT
P16,1,MOLEX_NANOFIT_1x6_WAY,"PCB Socket, 2.5mm pitch, 105309 series, Vertical, PTH, 6-WAY, 1-ROW",MOLEX,105313-1106,b,Molex_Nano-Fit_105309-xx06_1x06_VERT
P17,1,MOLEX_NANOFIT_2x3_WAY,"PCB Socket, 2.5mm pitch, 105310 series, Vertical, PTH, 6-WAY, 2-ROW",MOLEX,105310-1204,b,Molex_Nano-Fit_105310-xx06_2x03_VERT
P18,1,CONN_01X02,"Pin Header, 2.54mm, Vertical, PTH, 2 Way, 1 Row, 01x02",WURTH,61300211121, ,61300211121
P19,1,MOLEX_KK2.54_1x4_WAY_FAN,"CONNECTOR, SOCKET, 4POS, 1ROW, KK 2.54, 2.54mm pitch, PWM fan header, PTH",MOLEX,47053-1000,b,MOLEX_47053-1000
"P2, P3, P4, P5",4,MOLEX_MINIFIT_JR_2x2_WAY,"CONNECTOR, SOCKET, 4POS, 2ROW, MINI-FIT JR, 5566 series, 4.2MM pitch, Vertical PTH",MOLEX,172447-0204,b,Molex_Mini-Fit_Jr_5566-04A_2x02_P4.20mm_Vertical
P20,1,CONN_01X06,"Pin Header, 2.54mm, Vertical, PTH, 6 Way, 1 Row, 01x06",WURTH,61300611121, ,61300611121
P21,1,MOLEX_NANOFIT_2x5_WAY,"CONNECTOR, SOCKET, 10POS, 2ROW, Nano-fit, 105310 series, 2.5MM pitch, PTH",MOLEX,105310-1110,b,Molex_Nano-Fit_105310-xx10_2x05_VERT
"Q1, Q2",2,Si7852DP,"MOSFET N-CH, 80V, 12.5A, 16.5mOhm, SOT-23",Vishay,SI7852DP-T1-GE3,b,SON127P490X575X90-9T313X381N
"Q3, Q6",2,2N7002P,MOSFET N-CH 60V 0.36A SOT-23,Fairchild," 2N7002,215",b,SOT95P240X110-3L16N
Q4,1,NTR1P02T1G,"MOSFET, P-CH, 1A, -20V, 0.148ohm, -10V, -1.9V",On Semi,NTR1P02T1G,b,SOT95P240X110-3L16N
Q5,1,BC847B,"Transistor, NPN, 45V, 100MHz, 250mW, 100mA, 250mW, SOT-23",Multicomp,BC847B,b,SOT95P240X110-3L16N
"R1, R2",2,130K_1608M,"RESISTOR, THICK FILM, 130K, 100mW, 5%, 0603, 1608M",PANASONIC,ERJ3GEYJ134V, ,RESC1608X50N
"R10, R44, R45, R46, R47",5,22K_1608M,"RESISTOR, THICK FILM, 22K, 100mW, 1%, 0603, 1608M",MULTICOMP,MCMR06X2202FTL, ,RESC1608X50N
R11,1,102K_1608M,"RESISTOR, THICK FILM, 102K, 100mW, 0.1%, 0603, 1608M",MULTICOMP,MCWF06R1023BTL, ,RESC1608X50N
R12,1,9K53_1608M,"RESISTOR, THICK FILM, 9.53K, 100mW, 1%, 0603, 1608M",VISHAY,CRCW06039K53FKEA, ,RESC1608X50N
R13,1,39K_1608M,No description,PANASONIC,MCMR06X2202FTL, ,RESC1608X50N
R14,1,1K2_1608M,"RESISTOR, THICK FILM, 1K2, 100mW, 1%, 0603, 1608M",VISHAY,CRCW06031K20FKEA, ,RESC1608X50N
R15,1,10K7_1608M,"RESISTOR, THICK FILM, 10.7K, 100mW, 1%, 0603, 1608M",PANASONIC,ERJ3EKF1072V, ,RESC1608X50N
R16,1,750K_1608M,"RESISTOR, THICK FILM, 750K, 100mW, 1%, 0603, 1608M",MULTICOMP,MCSR06X7503FTL, ,RESC1608X50N
R17,1,2R2_1608M,"RESISTOR, THICK FILM, 2.2R, 100mW, 5%, 0603, 1608M",PANASONIC,ERJ-S03J2R2V, ,RESC1608X50N
R18,1,1R0_1608M,"RESISTOR, THICK FILM, 1R, 100mW, 5%, 0603, 1608M",MULTICOMP,MCMR06X1R0JTL, ,RESC1608X50N
"R20, R21, R22",3,0R_1608M,"RESISTOR, THICK FILM, 0R, 63mW, 0603, 1608M",MULTICOMP,MC0063W06030R, ,RESC1608X50N
R24,1,R01_3216M,"RESISTOR, THICK FILM, 10mOhm, 1W, 1206, 3216M",Vishay,WSLP1206R0100FEA, ,RESC3216X140N
R26,1,91K_1608M,"RESISTOR, THICK FILM, 91K, 250mW, 1%, 0603, 1608M",PANASONIC,ERJPA3F9102V, ,RESC1608X50N
"R29, R35, R57",3,1K_QUAD_ARRAY_1608M,"RESISTOR, THICK FILM, 1K, 5%, 0603, 1608M, QUAD ARRAY",BOURNS,CAY16-102J4LF,b,R_Array_Concave_4x1608M
"R3, R23, R36, R37, R38, R39, R55, R56, R61, R63, R70",11,10K0_1608M,"RESISTOR, THICK FILM, 10K, 125mW, 1%, 0603, 1608M",TE CONNECTIVITY,CRGH0603F10K, ,RESC1608X50N
"R30, R31, R67, R68",4,22R_1608M,"RESISTOR, THICK FILM, 22R, 125mW, 1%, 0603, 1608M",MULTICOMP,MC0063W060314R22, ,RESC1608X50N
"R32, R40, R41, R42, R43, R50, R51",7,100R_1608M,"RESISTOR, THICK FILM, 100R, 125mW, 1%, 0603, 1608M",MULTICOMP,MC0063W06035100R, ,RESC1608X50N
"R33, R34, R65, R66",4,4K7_1608M,"RESISTOR, THICK FILM, 100K, 125mW, 1%, 0603, 1608M",MULTICOMP,MC0063W060354K7, ,RESC1608X50N
"R4, R58, R59",3,2K40_1608M,"RESISTOR, THICK FILM, 2K4, 63mW, 1%, 0603, 1608M",MULTICOMP,MC0063W060312K4, ,RESC1608X50N
R48,1,47R_QUAD_ARRAY_1608M,"RESISTOR, THICK FILM, 47R, 5%, 0603, 1608M, QUAD ARRAY",PANASONIC,EXBV8V470JV,b,R_Array_Concave_4x1608M
"R49, R52, R53, R54, R62",5,10R_1608M,"RESISTOR, THICK FILM, 10R, 125mW, 0603, 1608M",MULTICOMP,MCHP03W8F100JT5E, ,RESC1608X50N
"R5, R8, R9, R19, R25, R28",6,100K_1608M,"RESISTOR, THICK FILM, 100K, 125mW, 1%, 0603, 1608M",MULTICOMP,MC0063W06035100K, ,RESC1608X50N
R6,1,1M_1608M,"RESISTOR, THICK FILM, 1M, 100mW, 1%, 0603, 1608M",VISHAY DRALORIC,CRCW06031M00FKEA, ,RESC1608X50N
R60,1,1K00_1608M,"RESISTOR, THICK FILM, 1K, 125mW, 1%, 0603, 1608M",MULTICOMP,MCHP03W8F1001T5E, ,RESC1608X50N
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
